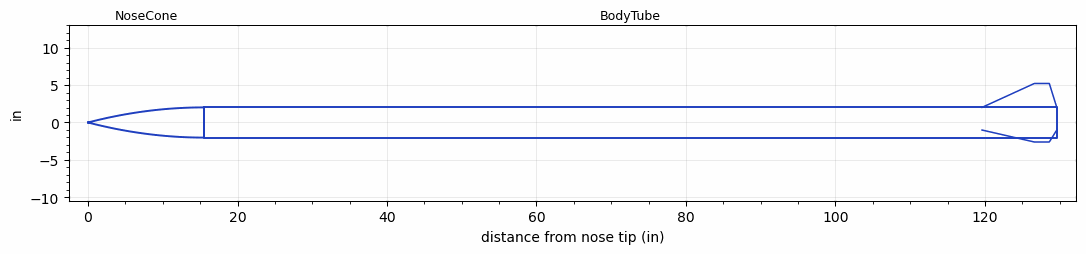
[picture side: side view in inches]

<RASAeroDocument>
 <FileVersion>2</FileVersion>
 <RocketDesign>
  <NoseCone>
   <Length>15.52</Length>
   <Diameter>4.04</Diameter>
   <Shape>Parabolic</Shape>
   <Location>0</Location>
  </NoseCone>
  <BodyTube>
   <Length>114.1</Length>
   <Diameter>4.04</Diameter>
   <LaunchShoeArea>0.09</LaunchShoeArea>
   <Location>15.52</Location>
   <Fin>
    <Count>3</Count>
    <Chord>10</Chord>
    <Span>3.2</Span>
    <SweepDistance>7</SweepDistance>
    <TipChord>2</TipChord>
    <Thickness>0.25</Thickness>
    <LERadius>0.125</LERadius>
    <Location>10</Location>
    <AirfoilSection>Double Wedge</AirfoilSection>
    <FX1>1</FX1>
   </Fin>
  </BodyTube>
  <Surface>Galvanized Metal</Surface>
  <ModifiedBarrowman>True</ModifiedBarrowman>
  <Turbulence>False</Turbulence>
  <UseBooster1>False</UseBooster1>
  <UseBooster2>False</UseBooster2>
 </RocketDesign>
 <LaunchSite>
  <Altitude>4596</Altitude>
  <Pressure>0</Pressure>
  <RodAngle>7</RodAngle>
  <RodLength>18</RodLength>
  <Temperature>75</Temperature>
  <WindSpeed>20</WindSpeed>
 </LaunchSite>
 <Recovery>
  <Altitude1>1000</Altitude1>
  <Altitude2>1500</Altitude2>
  <DeviceType1>Parachute</DeviceType1>
  <DeviceType2>Parachute</DeviceType2>
  <Event1>True</Event1>
  <Event2>True</Event2>
  <Size1>30.57</Size1>
  <Size2>157.2</Size2>
  <EventType1>Apogee</EventType1>
  <EventType2>Altitude</EventType2>
  <CD1>0.75</CD1>
  <CD2>0.928</CD2>
 </Recovery>
 <SimulationList>
  <Simulation>
   <SustainerEngine>N2900-CL  (CTI)</SustainerEngine>
   <SustainerLaunchWt>70</SustainerLaunchWt>
   <SustainerNozzleDiameter>2</SustainerNozzleDiameter>
   <SustainerCG>75.91</SustainerCG>
   <SustainerIgnitionDelay>0</SustainerIgnitionDelay>
   <Booster1SeparationDelay>0</Booster1SeparationDelay>
   <Booster1IgnitionDelay>0</Booster1IgnitionDelay>
   <IncludeBooster1>False</IncludeBooster1>
   <Booster2Delay>0</Booster2Delay>
   <IncludeBooster2>False</IncludeBooster2>
   <TimetoApogee>41.07911</TimetoApogee>
   <MaxAltitude>29333.59</MaxAltitude>
   <MaxVelocity>1750.834</MaxVelocity>
  </Simulation>
  <Simulation>
   <SustainerEngine>N2900-CL  (CTI)</SustainerEngine>
   <SustainerLaunchWt>67.8</SustainerLaunchWt>
   <SustainerNozzleDiameter>2</SustainerNozzleDiameter>
   <SustainerCG>74.2</SustainerCG>
   <SustainerIgnitionDelay>0</SustainerIgnitionDelay>
   <Booster1SeparationDelay>0</Booster1SeparationDelay>
   <Booster1IgnitionDelay>0</Booster1IgnitionDelay>
   <IncludeBooster1>False</IncludeBooster1>
   <Booster2Delay>0</Booster2Delay>
   <IncludeBooster2>False</IncludeBooster2>
   <TimetoApogee>44.54853</TimetoApogee>
   <MaxAltitude>34035.13</MaxAltitude>
   <MaxVelocity>1836.225</MaxVelocity>
  </Simulation>
  <Simulation>
   <SustainerEngine>N2900-CL  (CTI)</SustainerEngine>
   <SustainerLaunchWt>74.8</SustainerLaunchWt>
   <SustainerNozzleDiameter>2</SustainerNozzleDiameter>
   <SustainerCG>74.5</SustainerCG>
   <SustainerIgnitionDelay>0</SustainerIgnitionDelay>
   <Booster1SeparationDelay>0</Booster1SeparationDelay>
   <Booster1IgnitionDelay>0</Booster1IgnitionDelay>
   <IncludeBooster1>False</IncludeBooster1>
   <Booster2Delay>0</Booster2Delay>
   <IncludeBooster2>False</IncludeBooster2>
   <TimetoApogee>42.83882</TimetoApogee>
   <MaxAltitude>30388.57</MaxAltitude>
   <MaxVelocity>1647.571</MaxVelocity>
  </Simulation>
  <Simulation>
   <SustainerEngine>N2900-CL  (CTI)</SustainerEngine>
   <SustainerLaunchWt>72.5</SustainerLaunchWt>
   <SustainerNozzleDiameter>2</SustainerNozzleDiameter>
   <SustainerCG>76.4</SustainerCG>
   <SustainerIgnitionDelay>0</SustainerIgnitionDelay>
   <Booster1SeparationDelay>0</Booster1SeparationDelay>
   <Booster1IgnitionDelay>0</Booster1IgnitionDelay>
   <IncludeBooster1>False</IncludeBooster1>
   <Booster2Delay>0</Booster2Delay>
   <IncludeBooster2>False</IncludeBooster2>
   <TimetoApogee>42.04895</TimetoApogee>
   <MaxAltitude>29953.94</MaxAltitude>
   <MaxVelocity>1686.675</MaxVelocity>
  </Simulation>
  <Simulation>
   <SustainerEngine>N2900-CL  (CTI)</SustainerEngine>
   <SustainerLaunchWt>77.8</SustainerLaunchWt>
   <SustainerNozzleDiameter>2</SustainerNozzleDiameter>
   <SustainerCG>74.8</SustainerCG>
   <SustainerIgnitionDelay>0</SustainerIgnitionDelay>
   <Booster1SeparationDelay>0</Booster1SeparationDelay>
   <Booster1IgnitionDelay>0</Booster1IgnitionDelay>
   <IncludeBooster1>False</IncludeBooster1>
   <Booster2Delay>0</Booster2Delay>
   <IncludeBooster2>False</IncludeBooster2>
   <TimetoApogee>42.10894</TimetoApogee>
   <MaxAltitude>28966.67</MaxAltitude>
   <MaxVelocity>1577.022</MaxVelocity>
  </Simulation>
  <Simulation>
   <SustainerEngine>O3400-IM-P  (CTI)</SustainerEngine>
   <SustainerLaunchWt>63.4</SustainerLaunchWt>
   <SustainerNozzleDiameter>2</SustainerNozzleDiameter>
   <SustainerCG>79</SustainerCG>
   <SustainerIgnitionDelay>0</SustainerIgnitionDelay>
   <Booster1SeparationDelay>0</Booster1SeparationDelay>
   <Booster1IgnitionDelay>0</Booster1IgnitionDelay>
   <IncludeBooster1>False</IncludeBooster1>
   <Booster2Delay>0</Booster2Delay>
   <IncludeBooster2>False</IncludeBooster2>
   <TimetoApogee>49.11776</TimetoApogee>
   <MaxAltitude>45245</MaxAltitude>
   <MaxVelocity>2414.926</MaxVelocity>
  </Simulation>
 </SimulationList>
</RASAeroDocument>
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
